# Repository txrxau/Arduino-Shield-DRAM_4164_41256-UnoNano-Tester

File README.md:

# Arduino Shield DRAM 4164 & 41256 Uno/Nano Tester
<br>
Arduno based tester for 4164/4264 (64k x 1bit) & 41256 (256k x 1bit) DRAM<br>
PCB based on ISS DRAMArduino schematic.<br>
https://forum.defence-force.org/viewtopic.php?t=1699 <br>
Shield suitable for Arduino UNO or Arduino Nano.
<br>

<br>
Final Revision of my PCB design<br>
All parts clearly marked on PCB silkscreen.<br>
Test button is optional for use with an Arduino UNO, the Nano just uses reset button on the Arduino Nano.<br>
I'd recommend the Extended code and view the serial output to see what faults are found if any.<br>
Based on kinetix Extended DRAMArduino code<br>
https://www.vogons.org/viewtopic.php?t=107370

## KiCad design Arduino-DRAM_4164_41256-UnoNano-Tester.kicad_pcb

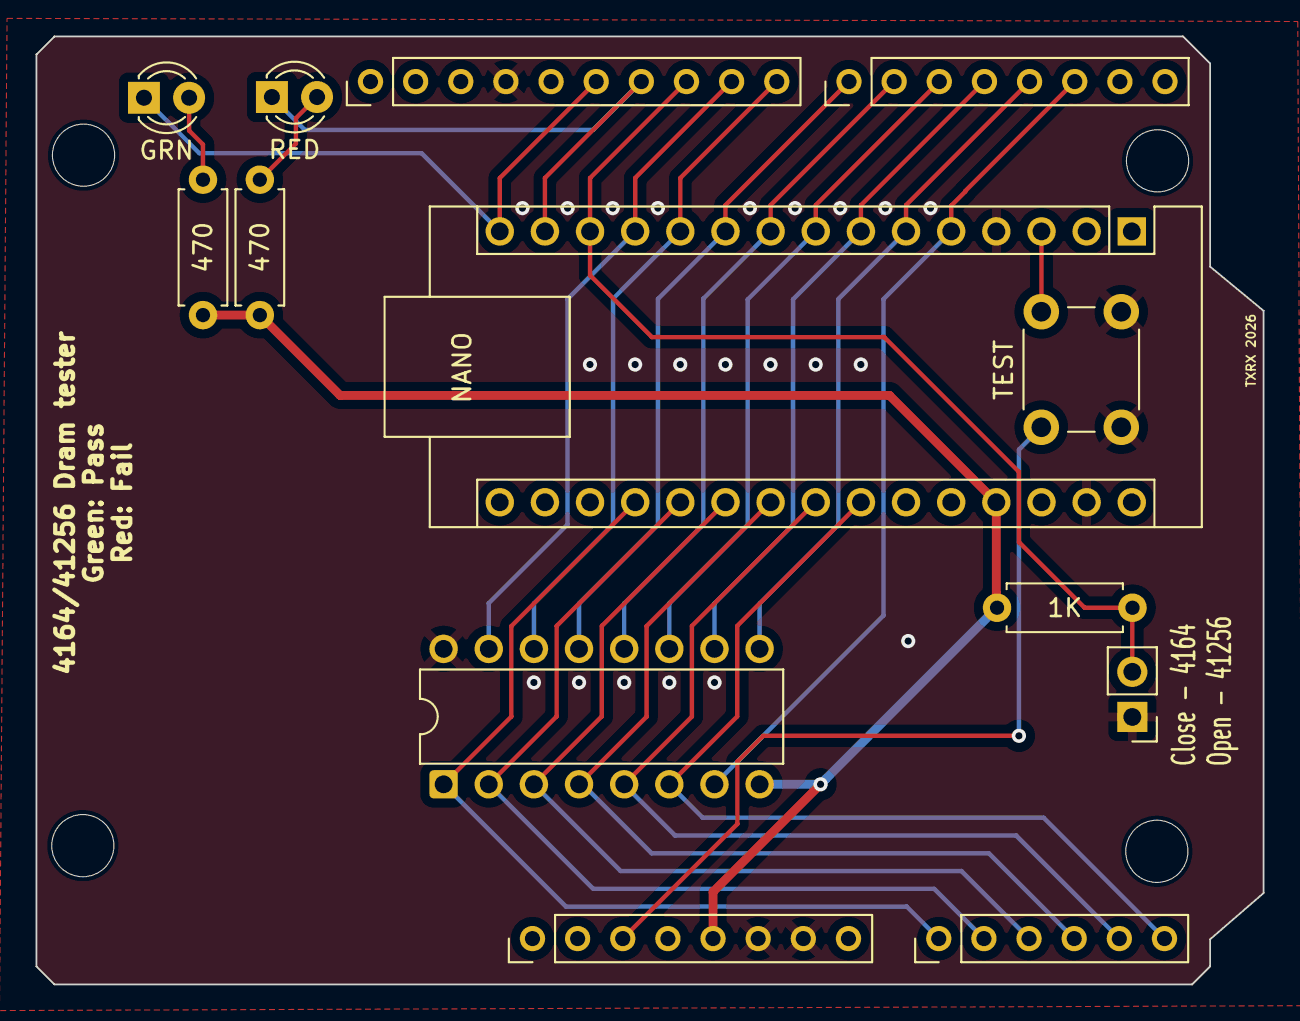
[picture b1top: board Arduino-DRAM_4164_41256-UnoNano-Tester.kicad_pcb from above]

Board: 2 copper layers, 69.0 x 53.3 mm, 13 parts (0 on the bottom side), 22 nets.

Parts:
A1: Arduino_Nano_v2.x; Arduino_Nano
D1: RED; LED_D3.0mm
D2: GRN; LED_D3.0mm
J1: Conn_01x02_Pin; PinHeader_1x02_P2.54mm_Vertical
R1, R2: 470; R_Axial_DIN0207_L6.3mm_D2.5mm_P7.62mm_Horizontal
R3: 1K; R_Axial_DIN0207_L6.3mm_D2.5mm_P7.62mm_Horizontal
SW1: SW_MEC_5E; SW_PUSH_6mm_H4.3mm
U5: Analog_1; Arduino_PinSocket_1x08_P2.54mm_Vertical
U6: Analog_2; Arduino_PinSocket_1x06_P2.54mm_Vertical
U6#2: Digital_1; Arduino_PinSocket_1x10_P2.54mm_Vertical
U7: Digital_2; Arduino_PinSocket_1x08_P2.54mm_Vertical
U8: MK4164N; DIP-16_W7.62mm

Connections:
/A0: A1.19 (A0), U6.9 (A0), U8.1 (~RFSH)
/A1: A1.20 (A1), U6.10 (A1), U8.2 (DIN)
/A2: A1.21 (A2), U6.11 (A2), U8.3 (~WRITE)
/A3: A1.22 (A3), U6.12 (A3), U8.4 (~RAS)
/A4: A1.23 (A4), U6.13 (A4), U8.5 (A0)
/A5: A1.24 (A5), U6.14 (A5), U8.6 (A2)
/D2: A1.5 (D2), U7.16 (D2), U8.7 (A1)
/D3: A1.6 (D3), U7.15 (~D3), U8.9 (A7)
/D4: A1.7 (D4), U7.14 (D4), U8.10 (A5)
/D5: A1.8 (D5), U7.13 (~D5), U8.11 (A4)
/D6: A1.9 (D6), U7.12 (~D6), U8.12 (A3)
/D7: A1.10 (D7), U7.11 (D7), U8.13 (A6)
/D8: A1.11 (D8), U6#2.10 (D8), U8.14 (DOUT)
/D9: A1.12 (D9), U6#2.9 (~D9), U8.15 (~CAS)
/D11: A1.14 (D11), D1.1 (K), U6#2.7 (~D11/COPI)
/D12: A1.15 (D12), D2.1 (K), U6#2.6 (D12/CIPO)
/J1: A1.13 (D10), J1.2, R3.1, U6#2.8 (~D10/CS/CANTX0)
/RST: A1.3 (~RESET), SW1.1, U5.3 (Reset)
GND: A1.4 (GND), A1.29 (GND), J1.1, SW1.2 (K), U5.6 (GND), U5.7 (GND), U6#2.4 (GND), U8.16 (VSS)
unnamed: D1.2 (A), R1.1
unnamed: D2.2 (A), R2.1
VCC: A1.27 (+5V), R1.2, R2.2, R3.2, U5.5 (+5V), U8.8 (VCC)

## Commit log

2026-05-19 Upload
2026-05-30 README.md
